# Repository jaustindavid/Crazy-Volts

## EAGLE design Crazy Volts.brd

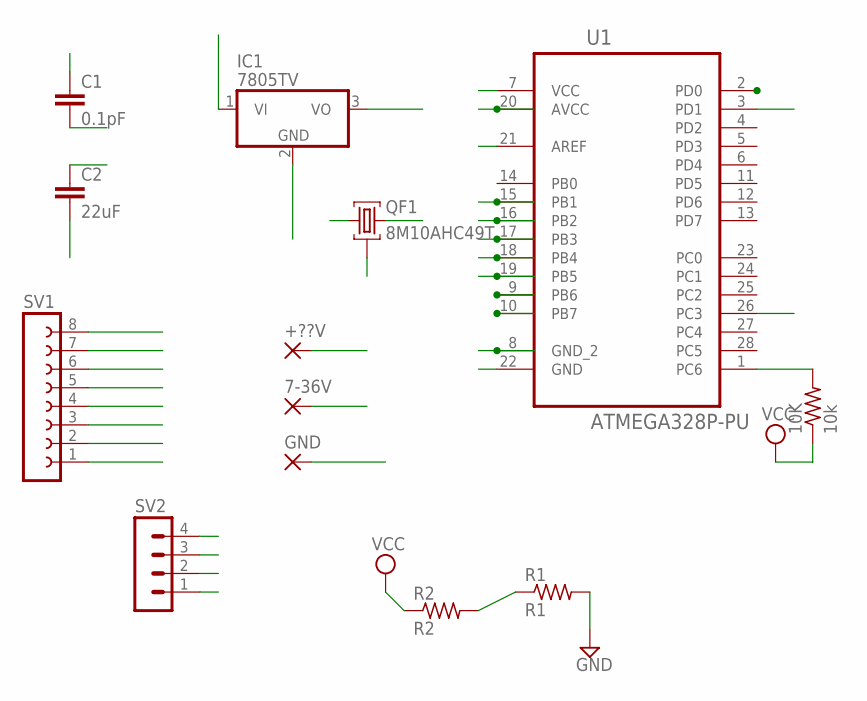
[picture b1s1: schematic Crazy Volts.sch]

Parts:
7-36V: 1,6/0,9
10K: 10k; 0207/7
+??V: 1,6/0,9
C1: 0.1pF; C5B2.5
C2: 22uF; C2.5-5
GND: 1,6/0,9
IC1: 7805TV; TO220V
QF1: 8M10AHC49T; HC49U
R1: R1; 0207/7
R2: R2; 0207/7
SV1: FE08-1; FE08
SV2: MA04-1
U1: ATMEGA328P-PU; DIP254P762X457-28

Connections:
3V3: SV1.6
DISP_CLK: SV1.2, U1.16 (PB2)
DISP_CS: SV1.5, U1.18 (PB4)
DISP_DATA: SV1.1, U1.15 (PB1)
DISP_DC: SV1.3, U1.17 (PB3)
DISP_RST: SV1.4, U1.19 (PB5)
GND: C1.2, C2.2, GND.1, IC1.2 (GND), QF1.2, R1.2, SV1.8, SV2.1, U1.8 (GND_2), U1.22 (GND)
IC9: QF1.3, U1.9 (PB6)
IC10: QF1.1, U1.10 (PB7)
RST: 10K.2, SV2.4, U1.1 (PC6)
RX: SV2.3, U1.2 (PD0)
TX: SV2.2, U1.3 (PD1)
VBATT: +??V.1, R2.1
VCC: 10K.1, C1.1, IC1.3 (VO), SV1.7, U1.7 (VCC), U1.20 (AVCC), U1.21 (AREF)
VIN: 7-36V.1, C2.1, IC1.1 (VI)
VSENSE: R1.1, R2.2, U1.26 (PC3)

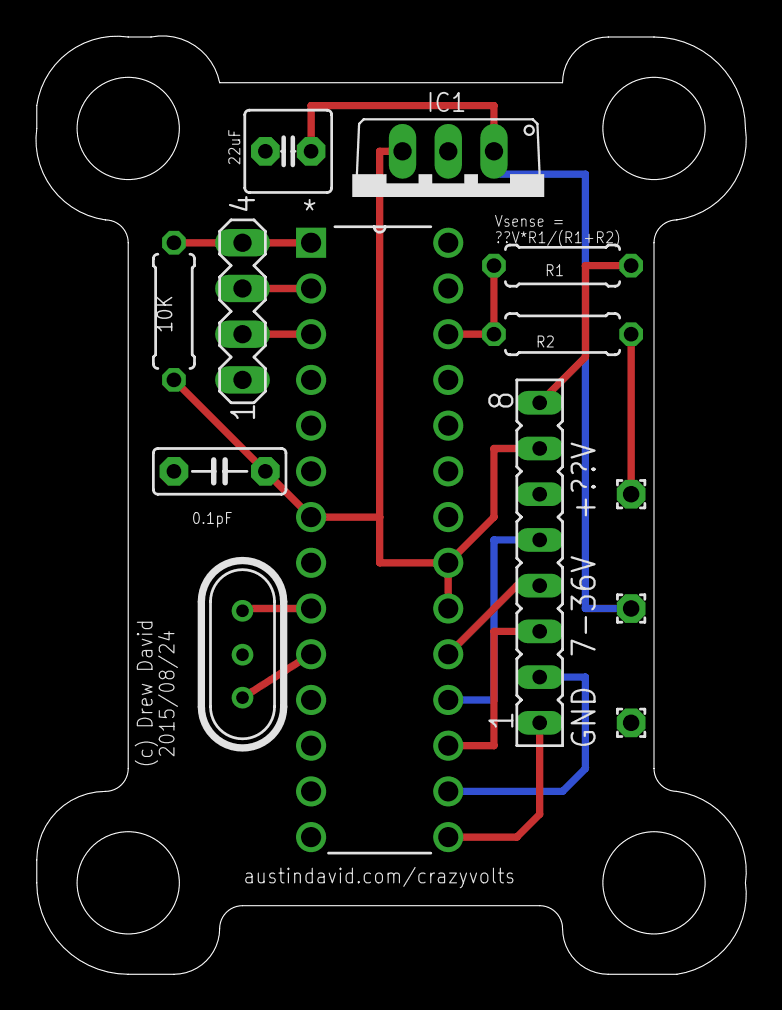
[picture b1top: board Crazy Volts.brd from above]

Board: 2 copper layers, 39.5 x 52.1 mm, 13 parts (0 on the bottom side), 15 nets.

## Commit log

2015-08-23 A voltmeter / fuel gauge for a Crazy Cart
    an Arduino-based voltmeter / fuel gauge for Drew’s & Jake’s Crazy Cart
2015-08-23 ignoring sync :/
2015-08-26 final board; initial timekeeper
    using a teensy + batt + xtal for timekeeping
2015-08-26 ignoral
    ignoring the synced
2015-09-10 tested on the PCB
    works on the PCB; added VSENSE
